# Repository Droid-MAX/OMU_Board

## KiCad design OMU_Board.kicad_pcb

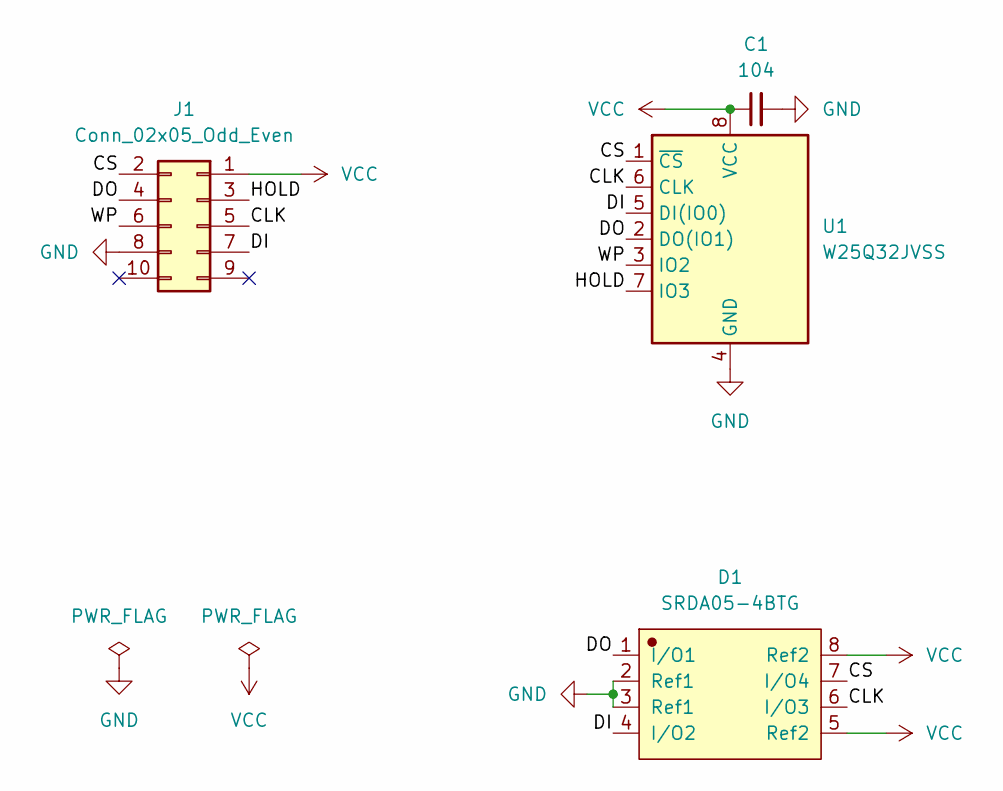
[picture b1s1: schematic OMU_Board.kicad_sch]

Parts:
C1: 104; C_0603_1608Metric
D1: SRDA05-4BTG; SOIC-8_L4.9-W3.9-P1.27-LS6.0-BL
J1: Conn_02x05_Odd_Even; PinSocket_2x05_P2.54mm_Vertical
U1: W25Q32JVSS; SOIC-8_5.23x5.23mm_P1.27mm

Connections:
/CLK: D1.6 (I/O3), J1.5, U1.6 (CLK)
/CS: D1.7 (I/O4), J1.2, U1.1 (~CS)
/DI: D1.4 (I/O2), J1.7, U1.5 (DI(IO0))
/DO: D1.1 (I/O1), J1.4, U1.2 (DO(IO1))
/HOLD: J1.3, U1.7 (IO3)
/WP: J1.6, U1.3 (IO2)
GND: C1.2, D1.2 (Ref1), D1.3 (Ref1), J1.8, U1.4 (GND)
VCC: C1.1, D1.5 (Ref2), D1.8 (Ref2), J1.1, U1.8 (VCC)

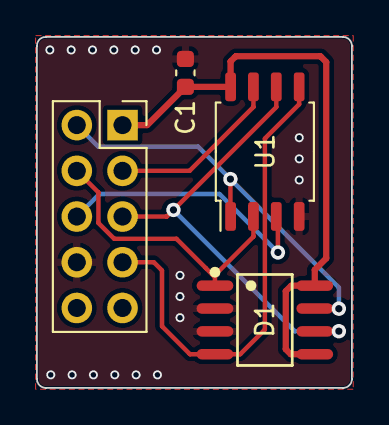
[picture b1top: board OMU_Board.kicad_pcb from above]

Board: 2 copper layers, 17.5 x 19.5 mm, 4 parts (0 on the bottom side), 8 nets.

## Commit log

2023-12-24 init commit
